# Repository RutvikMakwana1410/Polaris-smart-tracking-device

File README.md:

# POLARIS – Smart Tracking Device

POLARIS is an ESP32-based embedded system designed to provide direction, GPS-based positioning, and accurate time information in a compact portable device. The system combines a GPS module, magnetometer, RTC, and OLED display with an ESP32 as the main controller.

The project is currently under development. The initial schematic and PCB design have been completed, while PCB refinement and firmware development are the next stages.

## Project Overview

The main objective of POLARIS is to develop a standalone device capable of providing:

* Direction
* Latitude and longitude
* GPS satellite-based time
* Date and time through the RTC when GPS is unavailable

The information will be displayed through a 0.96-inch OLED display. Tactile switches will be used to navigate between different information screens.

## Why POLARIS?

The idea behind POLARIS is to provide essential direction, location, and time information through a small standalone embedded device.

The system is designed to combine multiple sensing modules into a single platform rather than depending on separate instruments for each function.

The project also provides practical experience in embedded systems, sensor interfacing, PCB design, and firmware development.

## Main Features

### Direction Detection

The GY-271 magnetometer is used to detect the Earth's magnetic field and determine the direction of the device. The direction will be displayed on the OLED interface.

### GPS Positioning

The NEO-6M GPS module receives signals from GPS satellites and provides geographical coordinates, including latitude and longitude.

### Satellite-Based Time

GPS satellites provide accurate timing information along with positioning data. POLARIS is designed to use the timing information received through the GPS module as the primary time reference.

### RTC Backup

The DS3231 RTC provides an independent and accurate local time source when GPS signals are unavailable.

### OLED Display

A 0.96-inch OLED display is used to present the information provided by the system. The planned interface includes direction, latitude, longitude, time, and date.

### User Controls

Two tactile switches are included for navigating between different information screens and controlling the display interface.

## Hardware Components

| Component              | Function                                       |
| ---------------------- | ---------------------------------------------- |
| ESP32                  | Main controller and data processing            |
| NEO-6M GPS Module      | Latitude, longitude and GPS timing information |
| GY-271 Magnetometer    | Direction detection                            |
| DS3231 RTC Module      | Backup and local timekeeping                   |
| 0.96-inch OLED Display | Display interface                              |
| 18650 Battery Holder   | Portable power supply                          |
| Tactile Switches       | Screen navigation and control                  |
| Charging Module        | Planned for integration                        |

## System Operation

The NEO-6M GPS module receives signals from GPS satellites and provides latitude, longitude, and timing information.

The GY-271 magnetometer measures the Earth's magnetic field and provides the information required to determine the device's direction.

The ESP32 acts as the central controller. It processes the information received from the GPS and magnetometer and manages the OLED display.

The DS3231 RTC provides timekeeping when GPS signals are unavailable.

The user will be able to view different information through the OLED display using the tactile switches.

## Power Supply

POLARIS is designed to operate using an 18650 battery, allowing the device to be used as a portable system.

A charging module is planned to be integrated into the final hardware design.

## PCB Development

The hardware is being designed using KiCad.

The repository currently contains the project schematic and PCB design files. The initial PCB layout has been developed and is currently being refined before manufacturing.

Current hardware progress:

* Initial schematic completed
* Initial PCB design completed
* PCB refinement in progress
* PCB manufacturing pending
* Hardware assembly pending

## Firmware Development

Firmware development is the next major stage of the project.

The ESP32 firmware will be responsible for:

* Reading GPS data
* Processing latitude and longitude
* Handling GPS timing information
* Reading RTC data
* Processing magnetometer readings
* Determining direction
* Controlling the OLED display
* Managing screen navigation
* Handling tactile switch input

## Project Status

| Development Stage       | Status                    |
| ----------------------- | ------------------------- |
| Project Concept         | Completed                 |
| Component Selection     | Completed                 |
| Schematic               | Initial version completed |
| PCB Design              | In Progress               |
| PCB Refinement          | Pending                   |
| Firmware Development    | Pending                   |
| Sensor Integration      | Pending                   |
| PCB Manufacturing       | Pending                   |
| Hardware Assembly       | Pending                   |
| Testing and Calibration | Pending                   |

## Project Documentation

The repository includes the POLARIS project presentation containing the project overview, hardware components, schematic, PCB layout, 3D PCB visualization, and system description.

### Project Presentation

**POLARIS_Project_Presentation.pptx**

> **Note:** The PowerPoint presentation may not be previewed directly in GitHub. To access the presentation, click the **three-dot menu (⋯)** next to the file and select **Download**. The downloaded `.pptx` file can then be opened using Microsoft PowerPoint or any compatible presentation software.

## Future Development

The remaining development work includes PCB refinement, firmware implementation, sensor integration, PCB manufacturing, hardware assembly, calibration, and complete system testing.

The final objective is to develop a compact standalone device capable of providing direction, latitude, longitude, and accurate time information through a simple OLED interface.

## Project Goal

The goal of POLARIS is to integrate GPS positioning, direction sensing, accurate timekeeping, and a simple user interface into one compact ESP32-based embedded system.

The project is intended to demonstrate the complete development process from component selection and circuit design to PCB development, firmware implementation, hardware assembly, and testing.

## Repository

GitHub: RutvikMakwana1410/Polaris-smart-tracking-device

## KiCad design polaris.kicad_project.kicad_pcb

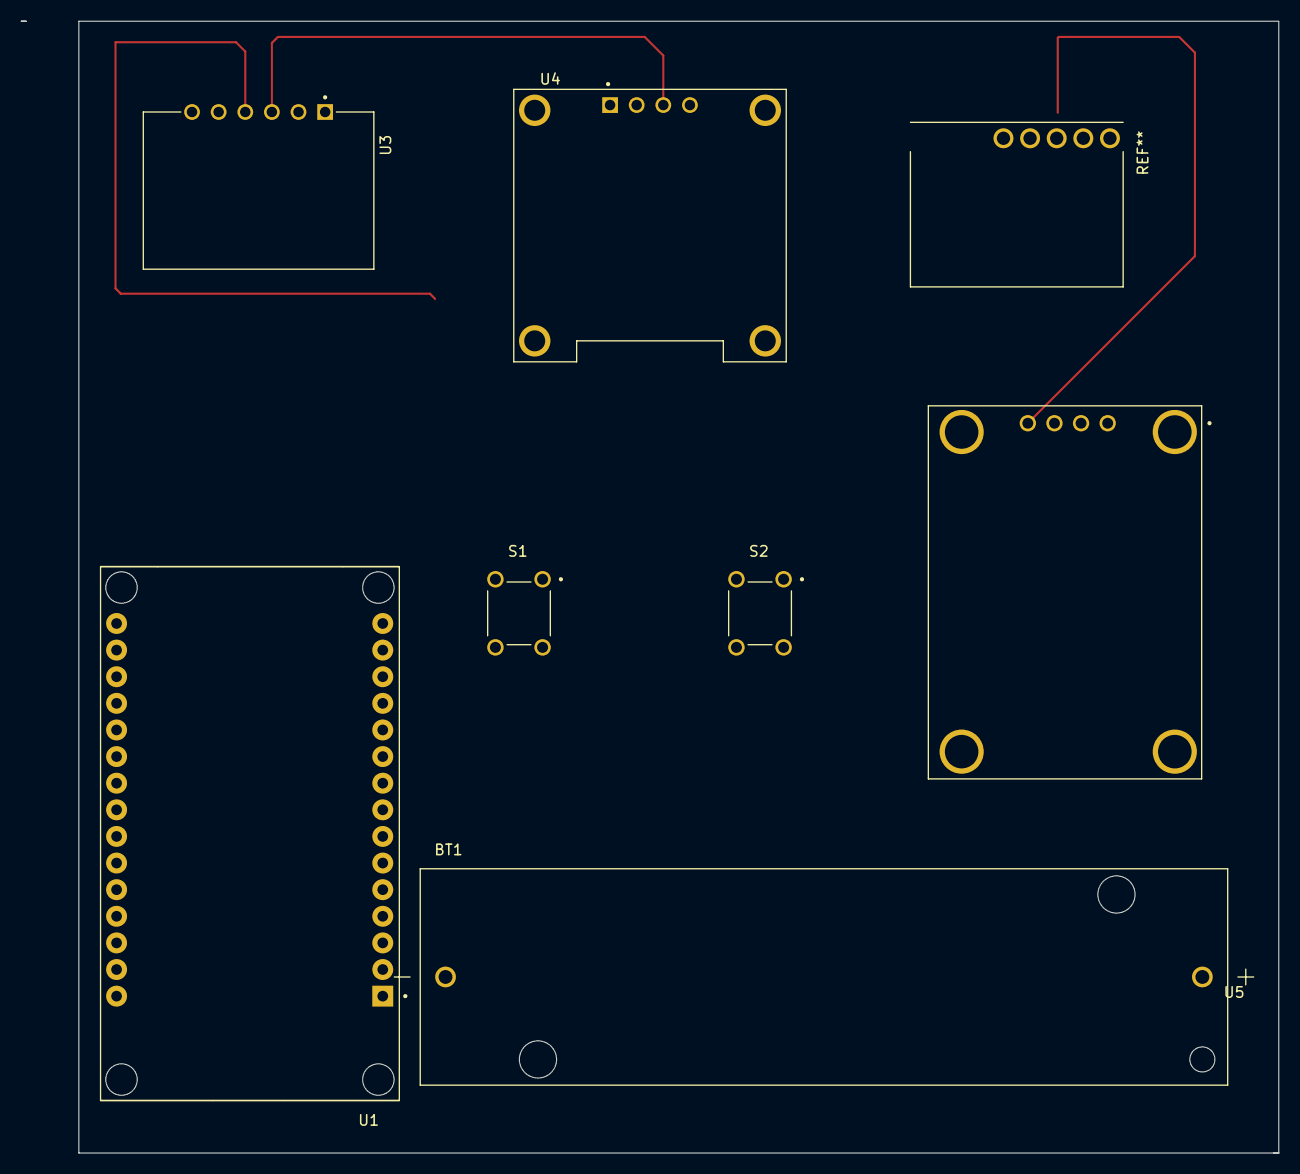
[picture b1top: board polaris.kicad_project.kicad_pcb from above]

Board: 2 copper layers, 120.0 x 108.0 mm, 7 parts (0 on the bottom side), 7 nets.

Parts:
BT1: 1043; BAT_1043
S1, S2: FSM8JH; SW_FSM8JH
U1: ESP32-DEVKIT-V1; MODULE_ESP32_DEVKIT_V1
U3: DS3231; MODULE_TC00500
U4: OLED 0.96; MODULE_DM-OLED096-636
U5: NEO-6M GPS; XCVR_ZC323200

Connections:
unnamed: U1.1 (3V3), U3.5 (VCC), U4.2 (VCC_IN), U5.1 (VCC)
unnamed: U1.11 (D21), U3.4 (SDA), U4.4 (SDA)
unnamed: U1.14 (D22), U3.3 (SCL), U4.3 (SCL)
unnamed: U1.6 (RX2), U5.3 (TX)
unnamed: U1.7 (TX2), U5.2 (RX)
unnamed: U1.2 (GND), U1.29 (GND), U3.6 (GND), U4.1 (GND), U5.4 (GND)
unnamed: U5.SH1 (SHIELD), U5.SH2 (SHIELD), U5.SH3 (SHIELD), U5.SH4 (SHIELD)
